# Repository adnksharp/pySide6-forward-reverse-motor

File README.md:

# Forward-Reverse motor control

Control de giro de un motor DC con un puente H, Arduino y Python.

## Requisitos

[FirmataExpress](https://mryslab.github.io/pymata4/firmata_express/#installation-instructions)

### Librerías de Python

- PySide6
- pymata4

```bash
pip install -r requirements.txt
```

### Hardware usado

|  |  |
|----|----|

- Placa de Arduino MEGA 2560
- Controlador de motores L298N
- Motor DC 12V 

## Características
- Control de un motor CC con un puente H y dos salidas PWM.
- Configuración del pulso modulado de salida mediante un `slider` y un `spin box`.
- Control de la dirección de salida con dos botones.

### En proceso

> [!TIP]
>
> - `slider` personalizado (rotativo).

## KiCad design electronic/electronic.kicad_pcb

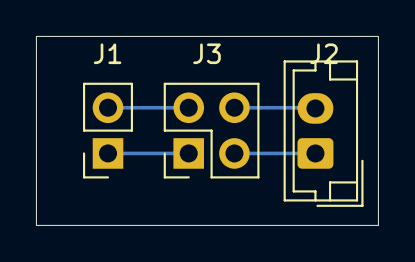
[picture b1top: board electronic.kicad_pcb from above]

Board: 2 copper layers, 19.0 x 10.5 mm, 3 parts (0 on the bottom side), 4 nets.

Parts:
J1: ARDUINO; PinSocket_1x02_P2.54mm_Vertical
J2: MOTOR; JST_EH_B2B-EH-A_1x02_P2.50mm_Vertical
J3: M_DRIVER; PinHeader_2x02_P2.54mm_Vertical

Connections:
M+: J2.1, J3.3
M-: J2.2, J3.4
OU1: J1.2, J3.2
OU2: J1.1, J3.1

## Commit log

2024-12-09 chore: init.
2024-12-09 style: form defined.
2024-12-09 feat: arduino config defined.
2024-12-09 feat: form connections defined.
2024-12-09 feat: arduino control added.
2024-12-09 docs: Delete __pycache__ directory
2024-12-09 docs: create README.md
2024-12-09 build: required libraries established on requeriments.txt.
2024-12-09 docs: update README.md
2024-12-10 chore: kidad electronic design added.
2024-12-10 chore: kidad electronic design modified.
